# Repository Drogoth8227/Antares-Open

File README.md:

# Antares-Open
Antares is a UWB based RTLS primarily focused on VR applications

(think lighthouse tracking but cheaper and using rf instead of light)

We have comms to the CDK's, so we can output over the NRF52833's UART USB and we can actually get into the uwb part now! (turns out zephyr is gud)

WARNING: UWB is still coming into the spotlight in mainstream devices (phones/headphones etc) so conflicts may occur and should be fixed ASAP

pros:

not line of sight based (blankets are back on the table)

no imu drift

solid state (no moving parts to wear out, looking at you lighthouses)

very low battery use, depending on hardware trackers could last weeks of usage per charge

open source- GNU public license so everyone benefits from updates

cons:

accuracy is untested (standard usage is within 10cm but can be improved with oversampling)

requires its own base stations (3 minimum, 4 suggested)

is still mostly theoretical at the moment (hopefully will change)

still costs money (estimations are around 60$ per tracker/base station)

progress so far:

system architecture drawn out

hardware schematic complete - layout TODO

location engine written in python - translate to other languages TODO

pc host client - not started

steamvr driver - not started

still want to get into it:

we currently have no custom hardware but you can order a dwm3001cdk from mouser/digikey and start with that

right now the priority is getting the location engine onto working hardware and demonstrate it works,

after that we can get into the features of UWB such as 1000hz polling, longer range, battery life, cost optimisation etc

hardware links

us digikey: https://www.digikey.com/en/products/detail/qorvo/DWM3001CDK/24367348?s=N4IgTCBcDaICYHcC2BmADGgjAYzgaxAF0BfIA

uk digikey: https://www.digikey.co.uk/en/products/detail/qorvo/DWM3001CDK/24367348?s=N4IgTCBcDaICYHcC2BmADGgjAYzgaxAF0BfIA

us mouser: https://www.mouser.com/ProductDetail/Qorvo/DWM3001CDK?qs=QNEnbhJQKvYHx2Hn8Cdgjg%3D%3D&_gl=1*7y67sj*_ga*dW5kZWZpbmVk*_ga_15W4STQT4T*dW5kZWZpbmVk*_ga_1KQLCYKRX3*dW5kZWZpbmVk

uk mouser: https://www.mouser.co.uk/ProductDetail/Qorvo/DWM3001CDK?qs=QNEnbhJQKvYHx2Hn8Cdgjg%3D%3D&_gl=1*7y67sj*_ga*dW5kZWZpbmVk*_ga_15W4STQT4T*dW5kZWZpbmVk*_ga_1KQLCYKRX3*dW5kZWZpbmVk

(mouser uk dont like selling rf to consumers for some reason, so be warned)

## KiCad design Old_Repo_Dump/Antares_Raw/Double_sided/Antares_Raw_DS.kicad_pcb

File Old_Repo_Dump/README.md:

# Antares
DWM1000 based RTLS (replacing plan.txt)

pros:
	
	works indoors
	line of sight denied
	relatively low cost
	more trackers can be used at cost of decreasing performance
	
cons:

	not as precise as laser tracking
	requires calibration when setup
	more battery usage than other systems
	requires base stations

REMEMBER TO CALIBRATE!	

Ranging method: 
	
	TDOA
	6.8mbps
	16 prf
	36 byte payload (12bits for id, acc, gyro respectively)
	preamble 128
	(example b on dw1000 data sheet)
	expected tx: 69ma avg
	expected rx: 122ma avg
	
radio bandwidth:

	1754 (or smth) pings/second for system max
	split 54 for anchor clock sync,
	1700 for trackers, (17 tags/100hz or dynamic adjust possibly)

4 non planar anchors

	single module per anchor
	Main anchor has usb connection to pc
	work out distance from each other (work that out at some point)

3 dwm1000's per tag?

	2 tag types, 
	1 for high accuracy with 3 modules
	1 for low accuracy with 1 module

use some dwm1000 library make life ez

Components:

	mcu - STM32f411
	IMU - LSM6DSRTR
	Battery charge ic - BQ24072
	Batteries - 18650 or smth idfk

Processing:

	kalman filters go brrr (someone work this shit out)
	imu refresh at 1000hz
	ranging refresh at some speed (depending on how fast imu drift/kalman sample size)

data to pc: anchors receive imu data via dwm1000 transmission possibly

Future Board Plans:
	Break up DWM1000 into inderviual DW1000 components

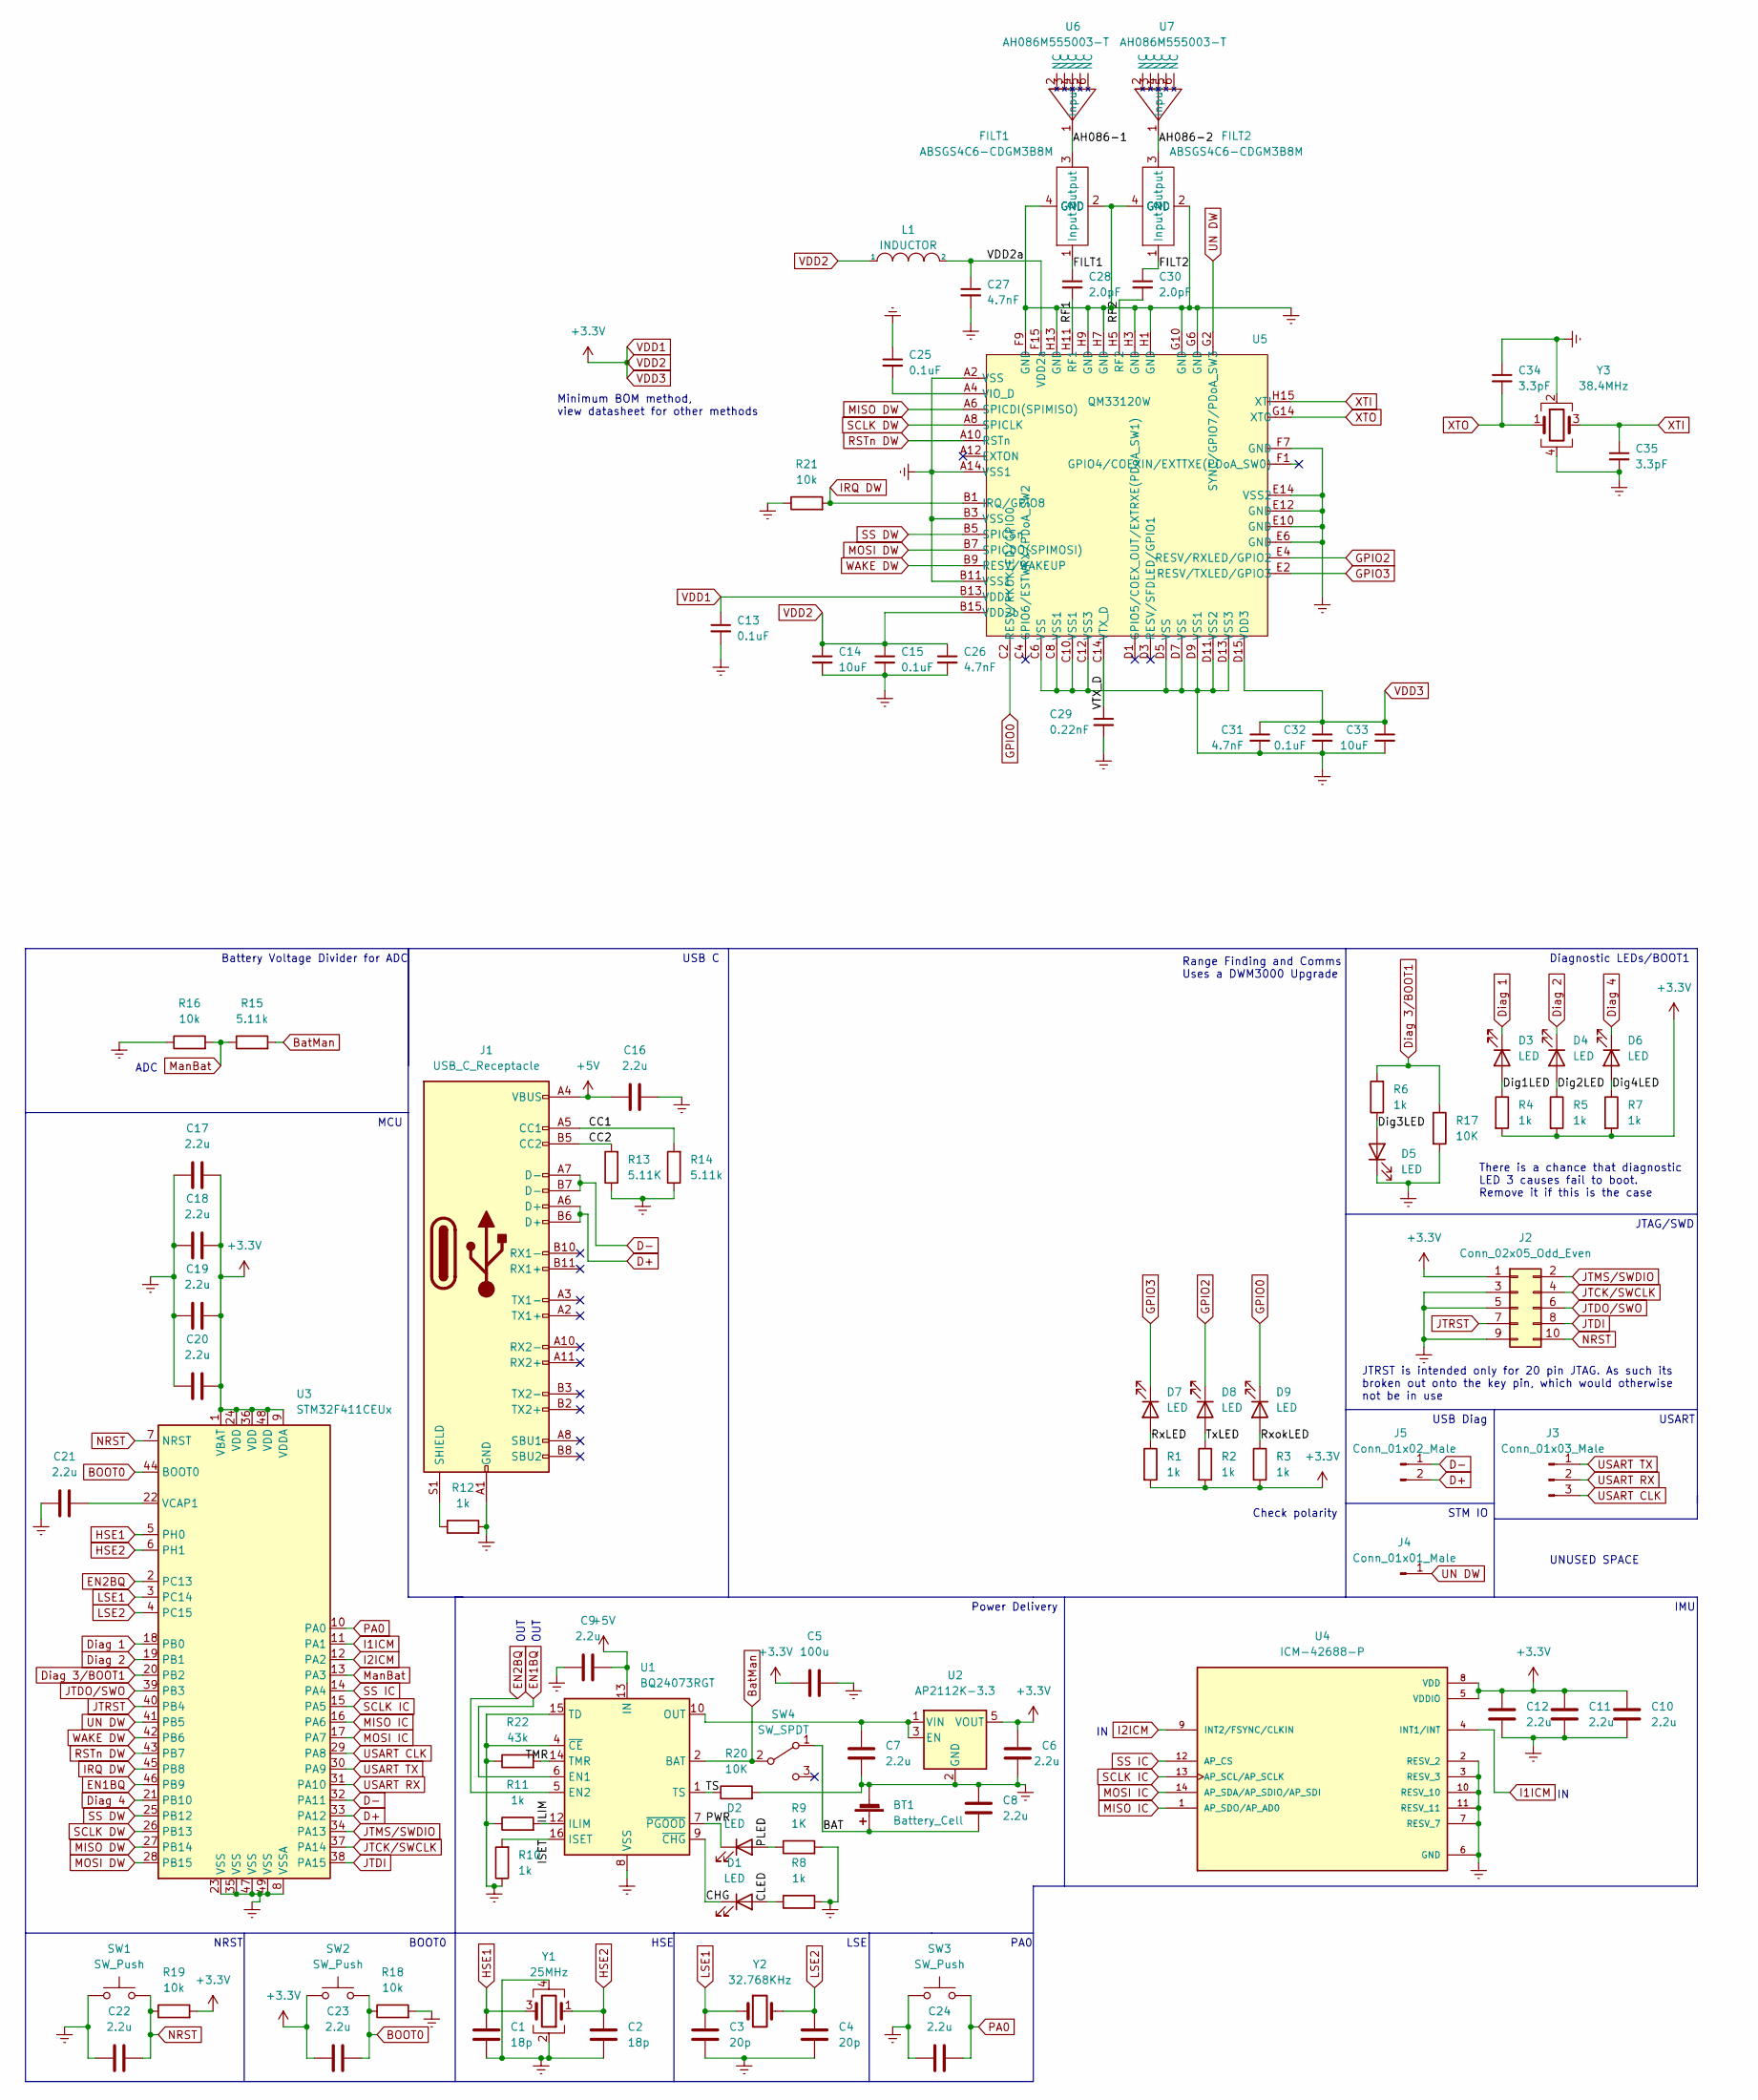
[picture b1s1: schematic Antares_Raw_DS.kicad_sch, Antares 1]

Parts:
BT1: Battery_Cell; PinHeader_1x02_P2.54mm_Vertical_SMD
C1, C2: 18p; C_0402_1005Metric
C3, C4: 20p; C_0402_1005Metric
C5: 100u; C_1206_3216Metric
C6, C7, C8, C9, C10, C11, C12, C16, C17, C18, C19, C20, C21, C22, C23, C24: 2.2u; C_0402_1005Metric
C13, C15, C25, C32: 0.1uF; C_0402_1005Metric
C14, C33: 10uF; C_0402_1005Metric
C26, C27, C31: 4.7nF; C_0402_1005Metric
C28, C30: 2.0pF; C_0402_1005Metric
C29: 0.22nF; C_0402_1005Metric
C34, C35: 3.3pF; C_0402_1005Metric
D1, D2, D3, D4, D5, D6, D7, D8, D9: LED; LED_0603_1608Metric
FILT1, FILT2: ABSGS4C6-CDGM3B8M
J1: USB_C_Receptacle; SHOUHAN_TYPE-C_24P_QT_143
J2: Conn_02x05_Odd_Even; PinHeader_2x05_P2.54mm_Vertical_SMD
J3: Conn_01x03_Male; PinHeader_2x05_P2.54mm_Horizontall_SMD
J4: Conn_01x01_Male; PinSocket_1x01_P2.54mm_Horizontal
J5: Conn_01x02_Male; PinHeader_1x02_P2.54mm_Vertical_SMD
L1: INDUCTOR; L_0201_0603Metric
R1, R2, R3, R4, R5, R6, R7, R8, R10, R11, R12: 1k; R_0402_1005Metric
R9: 1K; R_0402_1005Metric
R13: 5.11K; R_0402_1005Metric
R14, R15: 5.11k; R_0402_1005Metric
R16, R18, R19, R21: 10k; R_0402_1005Metric
R17, R20: 10K; R_0402_1005Metric
R22: 43k; R_0402_1005Metric
SW1, SW2, SW3: SW_Push; SW_SPST_TL3342
SW4: SW_SPDT; MK-12C01N-G1.5
U1: BQ24073RGT; VQFN-16-1EP_3x3mm_P0.5mm_EP1.6x1.6mm
U2: AP2112K-3.3; SOT-23-5
U3: STM32F411CEUx; QFN-48-1EP_7x7mm_P0.5mm_EP5.6x5.6mm
U4: ICM-42688-P; LGA-14_3x2.5mm_P0.5mm_LayoutBorder3x4y; PARTREV 1.2
U5: QM33120W; WLCSP-52
U6, U7: AH086M555003-T; AH086M
Y1: 25MHz; Crystal_SMD_3225-4Pin_3.2x2.5mm
Y2: 32.768KHz; Crystal_SMD_3215-2Pin_3.2x1.5mm
Y3: 38.4MHz; Crystal_SMD_2016-4Pin_2.0x1.6mm

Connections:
+5V: C9.1, C16.2, J1.A4 (VBUS), J1.A9 (VBUS), J1.B4 (VBUS), J1.B9 (VBUS), U1.13 (IN)
/BAT: BT1.1 (+), C8.2, SW4.1 (A)
/CC1: J1.A5 (CC1), R14.2
/CC2: J1.B5 (CC2), R13.2
/CHG: D1.1 (K), U1.9 (~CHG)
/CLED: D1.2 (A), R8.1
/Dig1LED: D3.2 (A), R4.1
/Dig2LED: D4.2 (A), R5.1
/Dig3LED: D5.2 (A), R6.1
/Dig4LED: D6.2 (A), R7.1
/ILIM: R11.2, U1.12 (ILIM)
/ISET: R10.2, U1.16 (ISET)
/PLED: D2.2 (A), R9.1
/PWR: D2.1 (K), U1.7 (~PGOOD)
/RxLED: D7.2 (A), R1.1
/RxokLED: D9.2 (A), R3.1
/TMR: R22.2, U1.14 (TMR)
/TS: R20.1, U1.1 (TS)
/TxLED: D8.2 (A), R2.1
BOOT0: C23.2, R18.1, SW2.2, U3.44 (BOOT0)
BatMan: R15.2, SW4.2 (B), U1.2 (BAT), U1.3 (BAT)
D+: J1.A6 (D+), J1.B6 (D+), J5.2, U3.33 (PA12)
D-: J1.A7 (D-), J1.B7 (D-), J5.1, U3.32 (PA11)
Diag 1: D3.1 (K), U3.18 (PB0)
Diag 2: D4.1 (K), U3.19 (PB1)
Diag 3/BOOT1: R6.2, R17.1, U3.20 (PB2)
Diag 4: D6.1 (K), U3.21 (PB10)
EN1BQ: U1.6 (EN1), U3.46 (PB9)
EN2BQ: U1.5 (EN2), U3.2 (PC13)
Earth: BT1.2 (-), C1.2, C2.2, C3.2, C4.2, C5.2, C6.2, C7.2, C8.1, C9.2, C10.2, C11.2, C12.2, C13.2, C14.2, C15.2, C16.1, C17.1, C18.1, C19.1, C20.1, C21.2, C22.1, C24.2, C25.1, C26.2, C27.2, C29.2, C31.2, C32.2, C33.2, C34.1, C35.2, D5.1 (K), FILT1.2 (GND), FILT1.4 (GND), FILT2.2 (GND), FILT2.4 (GND), J1.A1 (GND), J1.A12 (GND), J1.B1 (GND), J1.B12 (GND), J2.3, J2.5, J2.9, R8.2, R9.2, R10.1, R11.1, R12.2, R13.1, R14.1, R16.1, R17.2, R18.2, R20.2, R21.1, R22.1, SW1.1, SW3.1, U1.4 (~CE), U1.8 (VSS), U1.15 (TD), U1.17 (VSS), U2.2 (GND), U3.8 (VSSA), U3.23 (VSS), U3.35 (VSS), U3.47 (VSS), U3.49 (VSS), U4.2 (RESV_2), U4.3 (RESV_3), U4.6 (GND), U4.7 (RESV_7), U4.10 (RESV_10), U4.11 (RESV_11), U5.A2 (VSS), U5.A14 (VSS1), U5.B3 (VSS), U5.B11 (VSS1), U5.C6 (VSS), U5.C8 (VSS1), U5.C10 (VSS1), U5.C12 (VSS3), U5.D5 (VSS), U5.D7 (VSS), U5.D9 (VSS1), U5.D11 (VSS2), U5.D13 (VSS3), U5.E6 (GND), U5.E10 (GND), U5.E12 (GND), U5.E14 (VSS2), U5.F7 (GND), U5.F9 (GND), U5.G6 (GND), U5.G10 (GND), U5.H1 (GND), U5.H3 (GND), U5.H7 (GND), U5.H9 (GND), U5.H13 (GND), Y1.2, Y1.4, Y3.2, Y3.4
GPIO0: D9.1 (K), U5.C2 (RESV/RKOKLED/GPIO0)
GPIO1: U5.D3 (RESV/SFDLED/GPIO1)
GPIO2: D8.1 (K), U5.E4 (RESV/RXLED/GPIO2)
GPIO3: D7.1 (K), U5.E2 (RESV/TXLED/GPIO3)
GPIO4: U5.F1 (GPIO4/COEXIN/EXTTXE(PDoA_SW0))
GPIO5: U5.D1 (GPIO5/COEX_OUT/EXTRXE(PDoA_SW1))
GPIO6: U5.C4 (GPIO6/ESTWRX/PDoA_SW2)
HSE1: C1.1, U3.5 (PH0), Y1.3
HSE2: C2.1, U3.6 (PH1), Y1.1
I1ICM: U3.11 (PA1), U4.4 (INT1/INT)
I2ICM: U3.12 (PA2), U4.9 (INT2/FSYNC/CLKIN)
IRQ DW: R21.2, U3.45 (PB8), U5.B1 (IRQ/GPIO8)
JTCK/SWCLK: J2.4, U3.37 (PA14)
JTDI: J2.8, U3.38 (PA15)
JTDO/SWO: J2.6, U3.39 (PB3)
JTMS/SWDIO: J2.2, U3.34 (PA13)
JTRST: J2.7, U3.40 (PB4)
LSE1: C3.1, U3.3 (PC14), Y2.1
LSE2: C4.1, U3.4 (PC15), Y2.2
MISO DW: U3.27 (PB14), U5.A6 (SPICDI(SPIMISO))
MISO IC: U3.16 (PA6), U4.1 (AP_SDO/AP_AD0)
MOSI DW: U3.28 (PB15), U5.B7 (SPICDO(SPIMOSI))
MOSI IC: U3.17 (PA7), U4.14 (AP_SDA/AP_SDIO/AP_SDI)
ManBat: R15.1, R16.2, U3.13 (PA3)
NRST: C22.2, J2.10, R19.1, SW1.2, U3.7 (NRST)
unnamed: C7.1, U1.10 (OUT), U1.11 (OUT), U2.1 (VIN), U2.3 (EN)
unnamed: C21.1, U3.22 (VCAP1)
unnamed: C28.1, FILT1.1 (Input)
unnamed: C30.1, FILT2.1 (Input)
unnamed: FILT1.3 (Output), U6.1 (Input)
unnamed: FILT2.3 (Output), U7.1 (Input)
unnamed: J1.S1 (SHIELD), R12.1
unnamed: C25.2, U5.A4 (VIO_D)
unnamed: C29.1, U5.C14 (VTX_D)
unnamed: C27.1, L1.2, U5.F15 (VDD2a)
unnamed: C30.2, U5.H5 (RF2)
unnamed: C28.2, U5.H11 (RF1)
PA0: C24.1, SW3.2, U3.10 (PA0)
RSTn DW: U3.43 (PB7), U5.A10 (RSTn)
SCLK DW: U3.26 (PB13), U5.A8 (SPICLK)
SCLK IC: U3.15 (PA5), U4.13 (AP_SCL/AP_SCLK)
SS DW: U3.25 (PB12), U5.B5 (SPICSn)
SS IC: U3.14 (PA4), U4.12 (AP_CS)
UN DW: J4.1, U3.41 (PB5), U5.G2 (SYNC/GPIO7/PDoA_SW3)
USART CLK: J3.3, U3.29 (PA8)
USART RX: J3.2, U3.31 (PA10)
USART TX: J3.1, U3.30 (PA9)
VDD1: C5.1, C6.1, C10.1, C11.1, C12.1, C13.1, C14.1, C15.1, C17.2, C18.2, C19.2, C20.2, C23.1, C26.1, C31.1, C32.1, C33.1, J2.1, L1.1, R1.2, R2.2, R3.2, R4.2, R5.2, R7.2, R19.2, SW2.1, U2.5 (VOUT), U3.1 (VBAT), U3.9 (VDDA), U3.24 (VDD), U3.36 (VDD), U3.48 (VDD), U4.5 (VDDIO), U4.8 (VDD), U5.B13 (VDD1), U5.B15 (VDD2b), U5.D15 (VDD3)
WAKE DW: U3.42 (PB6), U5.B9 (RESV/WAKEUP)
XTI: C35.1, U5.H15 (XTI), Y3.3
XTO: C34.2, U5.G14 (XTO), Y3.1

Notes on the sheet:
Diagnostic LEDs/BOOT1
OUT
HSE
USB Diag
MCU
Range Finding and Comms Uses a DWM3000 Upgrade
USB C
PA0
BOOT0
Minimum BOM method, view datasheet for other methods
JTRST is intended only for 20 pin JTAG. As such its broken out onto the key pin, which would otherwise not be in use
Check polarity
There is a chance that diagnostic LED 3 causes fail to boot. Remove it if this is the case
USART
IMU
OUT
NRST
UNUSED SPACE
Power Delivery
ADC
STM IO
LSE
Battery Voltage Divider for ADC
JTAG/SWD

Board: 6 copper layers, 89 parts (4 on the bottom side), 77 nets, no tracks yet.

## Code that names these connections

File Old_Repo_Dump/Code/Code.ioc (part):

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Mcu.Name=STM32F411C(C-E)Ux
Mcu.Package=UFQFPN48
Mcu.UserName=STM32F411CEUx
PA0-WKUP.Mode=SYS_WakeUp0
PA0-WKUP.Signal=SYS_WKUP
PA1.Signal=GPIO_Input
PA10.Mode=Synchronous
PA10.Signal=USART1_RX
PA11.Mode=Device_Only
PA11.Signal=USB_OTG_FS_DM
PA12.Mode=Device_Only
PA12.Signal=USB_OTG_FS_DP
PA13.Mode=JTAG_5_pins
PA13.Signal=SYS_JTMS-SWDIO
PA14.Mode=JTAG_5_pins
PA14.Signal=SYS_JTCK-SWCLK
PA15.Mode=JTAG_5_pins
PA15.Signal=SYS_JTDI
PA2.Signal=GPIO_Input
PA3.Signal=ADCx_IN3
PA4.Signal=SPI1_NSS
PA5.Mode=Full_Duplex_Master
PA5.Signal=SPI1_SCK
PA6.Mode=Full_Duplex_Master
PA6.Signal=SPI1_MISO
PA7.Mode=Full_Duplex_Master
PA7.Signal=SPI1_MOSI
PA8.Mode=Synchronous
PA8.Signal=USART1_CK
PA9.Mode=Synchronous
PA9.Signal=USART1_TX
PB0.Signal=GPIO_Output
PB1.Signal=GPIO_Output
PB10.Signal=GPIO_Output
PB12.Signal=SPI2_NSS
PB13.Mode=Full_Duplex_Master
PB13.Signal=SPI2_SCK
PB14.Mode=Full_Duplex_Master
PB14.Signal=SPI2_MISO
PB15.Mode=Full_Duplex_Master
PB15.Signal=SPI2_MOSI
PB2.Signal=GPIO_Output
PB3.Mode=JTAG_5_pins
PB3.Signal=SYS_JTDO-SWO
PB4.Mode=JTAG_5_pins
PB4.Signal=SYS_JTRST
PB5.Signal=GPIO_Input
PB6.Signal=GPIO_Input
PB7.Signal=GPIO_Input
PB8.Signal=GPIO_Output
PB9.Signal=GPIO_Output
PC13-ANTI_TAMP.Signal=GPIO_Output
PC14-OSC32_IN.Signal=RCC_OSC32_IN
PC15-OSC32_OUT.Signal=RCC_OSC32_OUT
PH0\ -\ OSC_IN.Signal=RCC_OSC_IN
PH1\ -\ OSC_OUT.Signal=RCC_OSC_OUT
RCC.HSE_VALUE=25000000
RCC.SYSCLKFreq_VALUE=16000000
board=custom

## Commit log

2025-04-22 fix README.md
2025-04-22 old_repo_push
    uploading previous work to build from
2025-04-25 Current dev goals
2025-08-09 cleanup
2025-09-06 Update README.md
    functional console output/upload
2025-11-07 07/11/25 updoot
    more cleanup, more work
2025-12-18 zephyr environment upload
2025-12-18 create .gitignore to prevent build env errors
